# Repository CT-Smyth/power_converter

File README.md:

VDM power_converter

A control system for controlling cheap power supply bricks (sold commonly as LED drivers, power supplies, etc) to make them suitable for battery charging or other low resistance variable loads. 

The circuit monitors current output from the power supply with a hall effect sensor, and adjusts a digipot which is wired to replace the trimmer pot normally used to adjust output voltage.

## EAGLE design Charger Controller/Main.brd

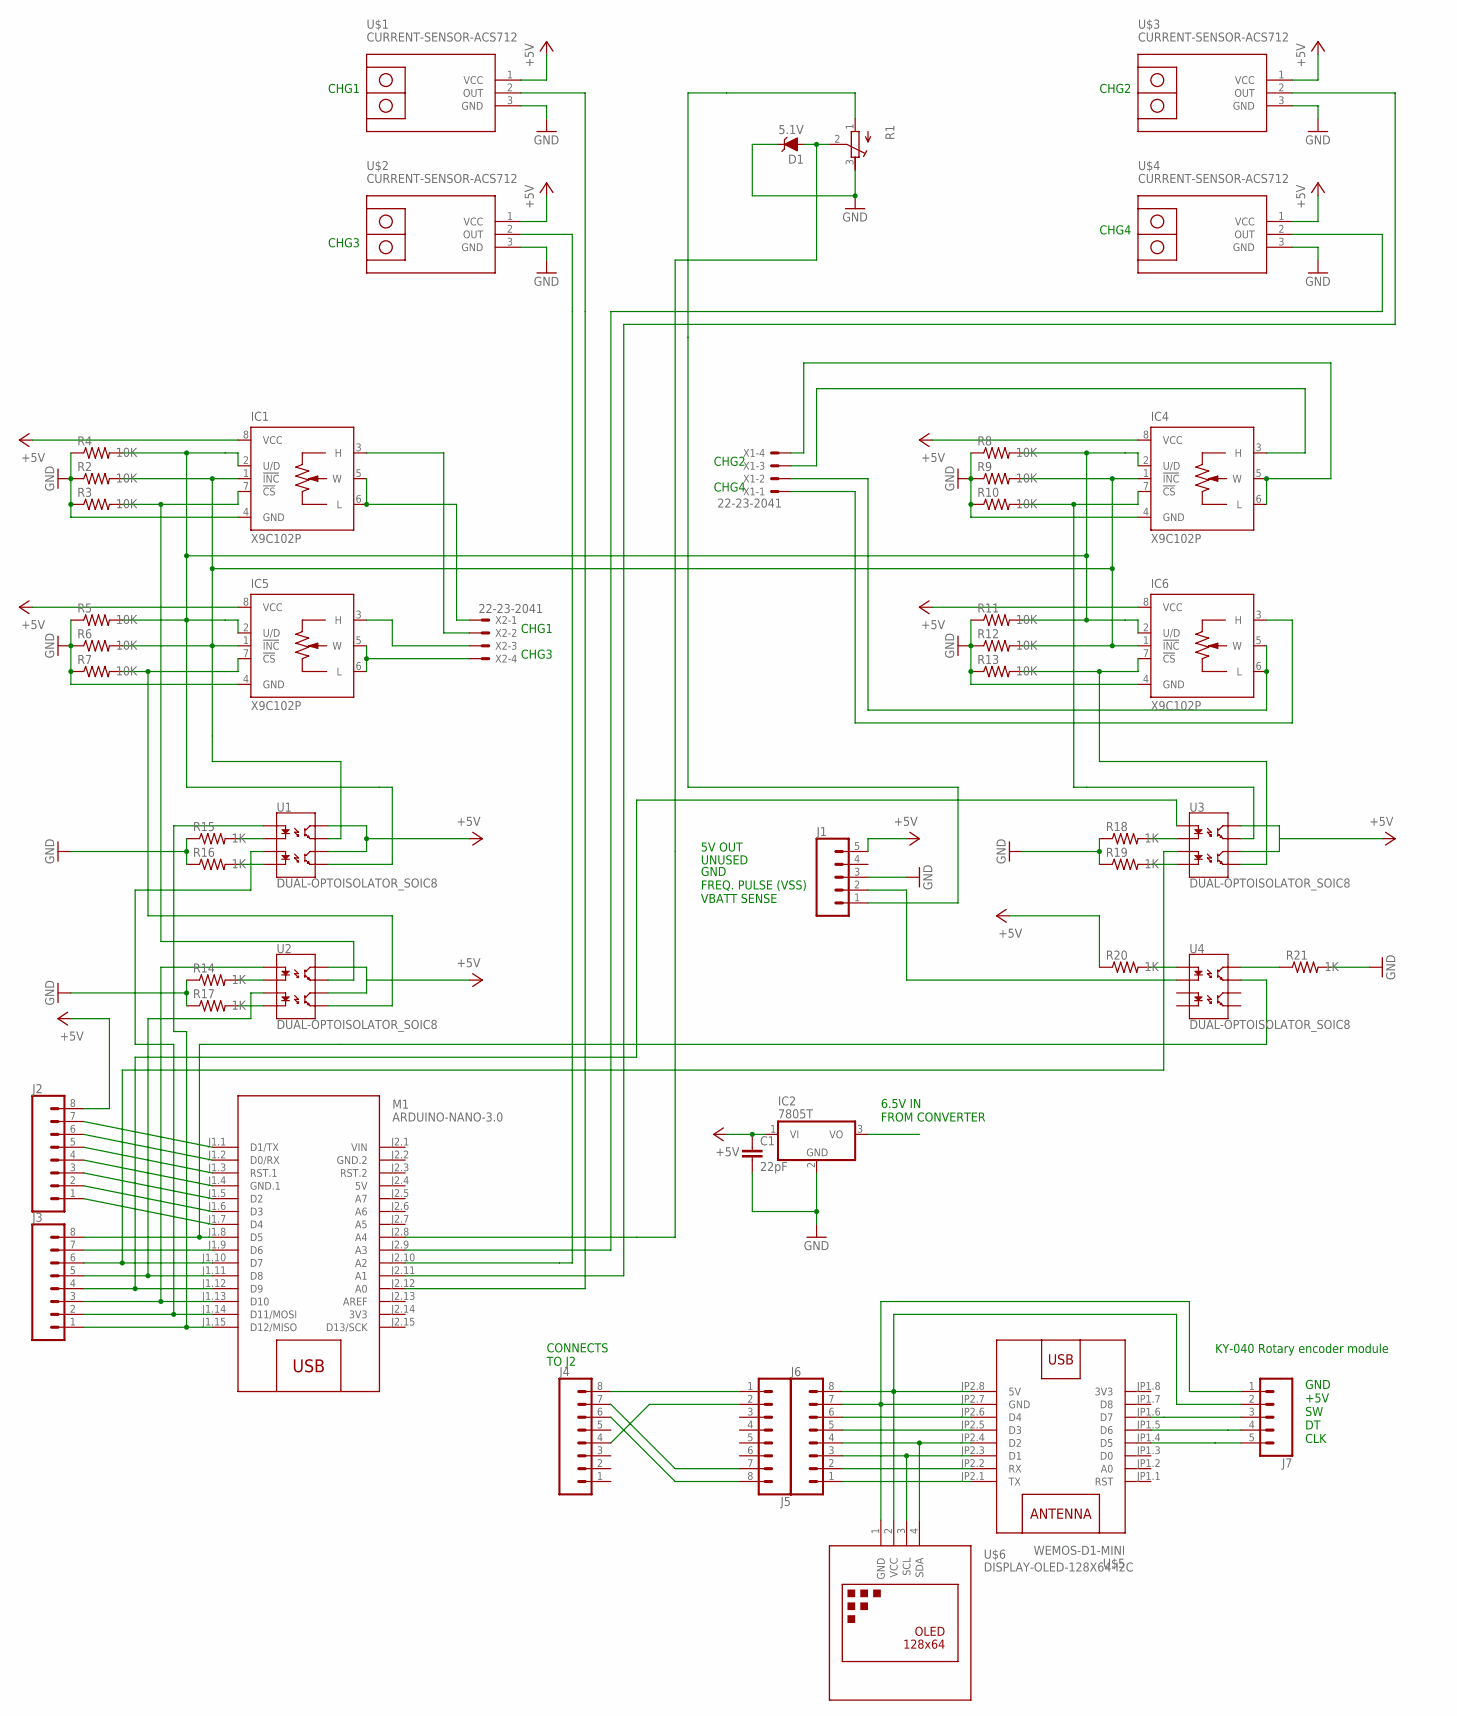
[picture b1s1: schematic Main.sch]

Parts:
C1: 22pF; CAP-PTH-2.54
D1: 5.1V; SOD-323
IC1, IC4, IC5, IC6: X9C102P; DIL08
IC2: 7805T; TO220H
J1, J7: CONN_05PTH_LONGPADS; 1X05_LONGPADS
J2, J3, J4, J5, J6: CONN_08LONGPADS; 1X08_LONGPADS
M1: ARDUINO-NANO-3.0
R1: R-TRIMM64W; RTRIM64W
R2, R3, R4, R5, R6, R7, R8, R9, R10, R11, R12, R13: 10K; 0204/7
R14, R15, R16, R17, R18, R19, R20, R21: 1K; 0204/7
U1, U2, U3, U4: DUAL-OPTOISOLATOR_SOIC8; SO08
U$1, U$2, U$3, U$4: CURRENT-SENSOR-ACS712
U$5: WEMOS-D1-MINI
U$6: DISPLAY-OLED-128X64-I2C
X1, X2: 22-23-2041

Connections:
3V3: M1.J2.14 (3V3), U$5.JP1.8 (3V3)
5V: M1.J2.4 (5V)
+5V: C1.1, IC1.8 (VCC), IC2.1 (VI), IC4.8 (VCC), IC5.8 (VCC), IC6.8 (VCC), J1.5, J2.8, R20.1, U1.6 (CL2), U1.8 (CL1), U2.6 (CL2), U2.8 (CL1), U3.6 (CL2), U3.8 (CL1), U$1.1 (VCC), U$2.1 (VCC), U$3.1 (VCC), U$4.1 (VCC)
GND: C1.2, D1.C, IC1.4 (GND), IC2.2 (GND), IC4.4 (GND), IC5.4 (GND), IC6.4 (GND), J1.3, R1.3 (E), R2.1, R3.1, R4.1, R5.1, R6.1, R7.1, R8.1, R9.1, R10.1, R11.1, R12.1, R13.1, R14.1, R15.1, R16.1, R17.1, R18.1, R19.1, R21.2, U$1.3 (GND), U$2.3 (GND), U$3.3 (GND), U$4.3 (GND)
GND.2: M1.J2.2 (GND.2)
unnamed: IC1.7 (!CS), R3.2, U2.7 (EM1)
unnamed: IC1.1 (!INC), IC4.1 (!INC), IC5.1 (!INC), IC6.1 (!INC), R2.2, R6.2, R9.2, R12.2, U1.7 (EM1)
unnamed: R15.2, U1.2 (C1)
unnamed: IC1.5 (W), IC1.6 (L), X2.1
unnamed: R16.2, U1.4 (C2)
unnamed: IC5.7 (!CS), R7.2, U2.5 (EM2)
unnamed: IC1.3 (H), X2.2
unnamed: IC1.2 (U/D), IC4.2 (U/D), IC5.2 (U/D), IC6.2 (U/D), R4.2, R5.2, R8.2, R11.2, U1.5 (EM2)
unnamed: IC5.5 (W), IC5.6 (L), X2.4
unnamed: IC5.3 (H), X2.3
unnamed: R14.2, U2.2 (C1)
unnamed: R17.2, U2.4 (C2)
unnamed: IC4.5 (W), IC4.6 (L), X1.4
unnamed: IC6.7 (!CS), R13.2, U3.5 (EM2)
unnamed: R18.2, U3.2 (C1)
unnamed: R19.2, U3.4 (C2)
unnamed: IC6.5 (W), IC6.6 (L), X1.2
unnamed: IC4.3 (H), X1.3
unnamed: IC6.3 (H), X1.1
unnamed: IC4.7 (!CS), R10.2, U3.7 (EM1)
unnamed: J1.2, U4.2 (C1)
unnamed: J1.1, R1.1 (A)
unnamed: D1.A, M1.J2.8 (A4), R1.2 (S)
unnamed: J3.8, M1.J1.8 (D5), U4.7 (EM1)
unnamed: R20.2, U4.1 (A1)
unnamed: R21.1, U4.8 (CL1)
unnamed: J2.1, M1.J1.7 (D4)
unnamed: J2.2, M1.J1.6 (D3)
unnamed: J2.3, M1.J1.5 (D2)
unnamed: J2.4, M1.J1.4 (GND.1)
unnamed: J2.5, M1.J1.3 (RST.1)
unnamed: J2.6, M1.J1.2 (D0/RX)
unnamed: J2.7, M1.J1.1 (D1/TX)
unnamed: J3.1, M1.J1.15 (D12/MISO), U1.1 (A1)
unnamed: J3.2, M1.J1.14 (D11/MOSI), U1.3 (A2)
unnamed: J3.3, M1.J1.13 (D10), U2.1 (A1)
unnamed: J3.4, M1.J1.12 (D9), U3.1 (A1)
unnamed: J3.5, M1.J1.11 (D8), U2.3 (A2)
unnamed: J3.6, M1.J1.10 (D7), U3.3 (A2)
unnamed: J3.7, M1.J1.9 (D6)
unnamed: M1.J2.12 (A0), U$1.2 (OUT)
unnamed: M1.J2.10 (A2), U$2.2 (OUT)
unnamed: M1.J2.11 (A1), U$3.2 (OUT)
unnamed: M1.J2.9 (A3), U$4.2 (OUT)
unnamed: J6.1, U$5.JP2.1 (TX)
unnamed: J6.2, U$5.JP2.2 (RX)
unnamed: J6.3, U$5.JP2.3 (D1), U$6.3 (SCL)
unnamed: J6.4, U$5.JP2.4 (D2), U$6.4 (SDA)
unnamed: J6.5, U$5.JP2.5 (D3)
unnamed: J6.6, U$5.JP2.6 (D4)
unnamed: J6.7, J7.1, U$5.JP2.7 (GND), U$6.1 (GND)
unnamed: J6.8, J7.2, U$5.JP2.8 (5V), U$6.2 (VCC)
unnamed: J4.8, J5.1
unnamed: J4.4, J5.2
unnamed: J4.7, J5.7
unnamed: J4.6, J5.8
unnamed: J7.3, U$5.JP1.6 (D7)
unnamed: J7.4, U$5.JP1.5 (D6)
unnamed: J7.5, U$5.JP1.4 (D5)
VIN: M1.J2.1 (VIN)

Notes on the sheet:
5V OUT
UNUSED
GND FREQ. PULSE (VSS) VBATT SENSE
CHG1
CHG3
CHG2
CHG4
6.5V IN FROM CONVERTER
CONNECTS TO J2
KY-040 Rotary encoder module
GND +5V SW DT CLK

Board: 2 copper layers, 48 parts (0 on the bottom side), 62 nets, no tracks yet.

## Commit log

2018-10-23 Control engine files initial commit
2018-10-23 Application controller initial commit
2018-10-23 Added schematics
2018-10-23 added comment
2018-10-23 edited comment
2018-10-23 comment edit
2018-10-23 edit
2018-10-23 Changed filenames to reflect correct versioning
2018-10-23 Bug fixes, changed sample rate
    Increased analog sampling duration to ensure that 1/30th of a second is sampled for better accuracy.
2018-10-23 Directory name change
2018-10-23 testing edit to comment

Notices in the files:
parts and their libraries:
diy-modules: Released under the Creative Commons Attribution 4.0 International License: http://creativecommons.org/licenses/by/4.0
SparkFun-DiscreteSemi: Licensing: Creative Commons ShareAlike 4.0 International - https://creativecommons.org/licenses/by-sa/4.0
